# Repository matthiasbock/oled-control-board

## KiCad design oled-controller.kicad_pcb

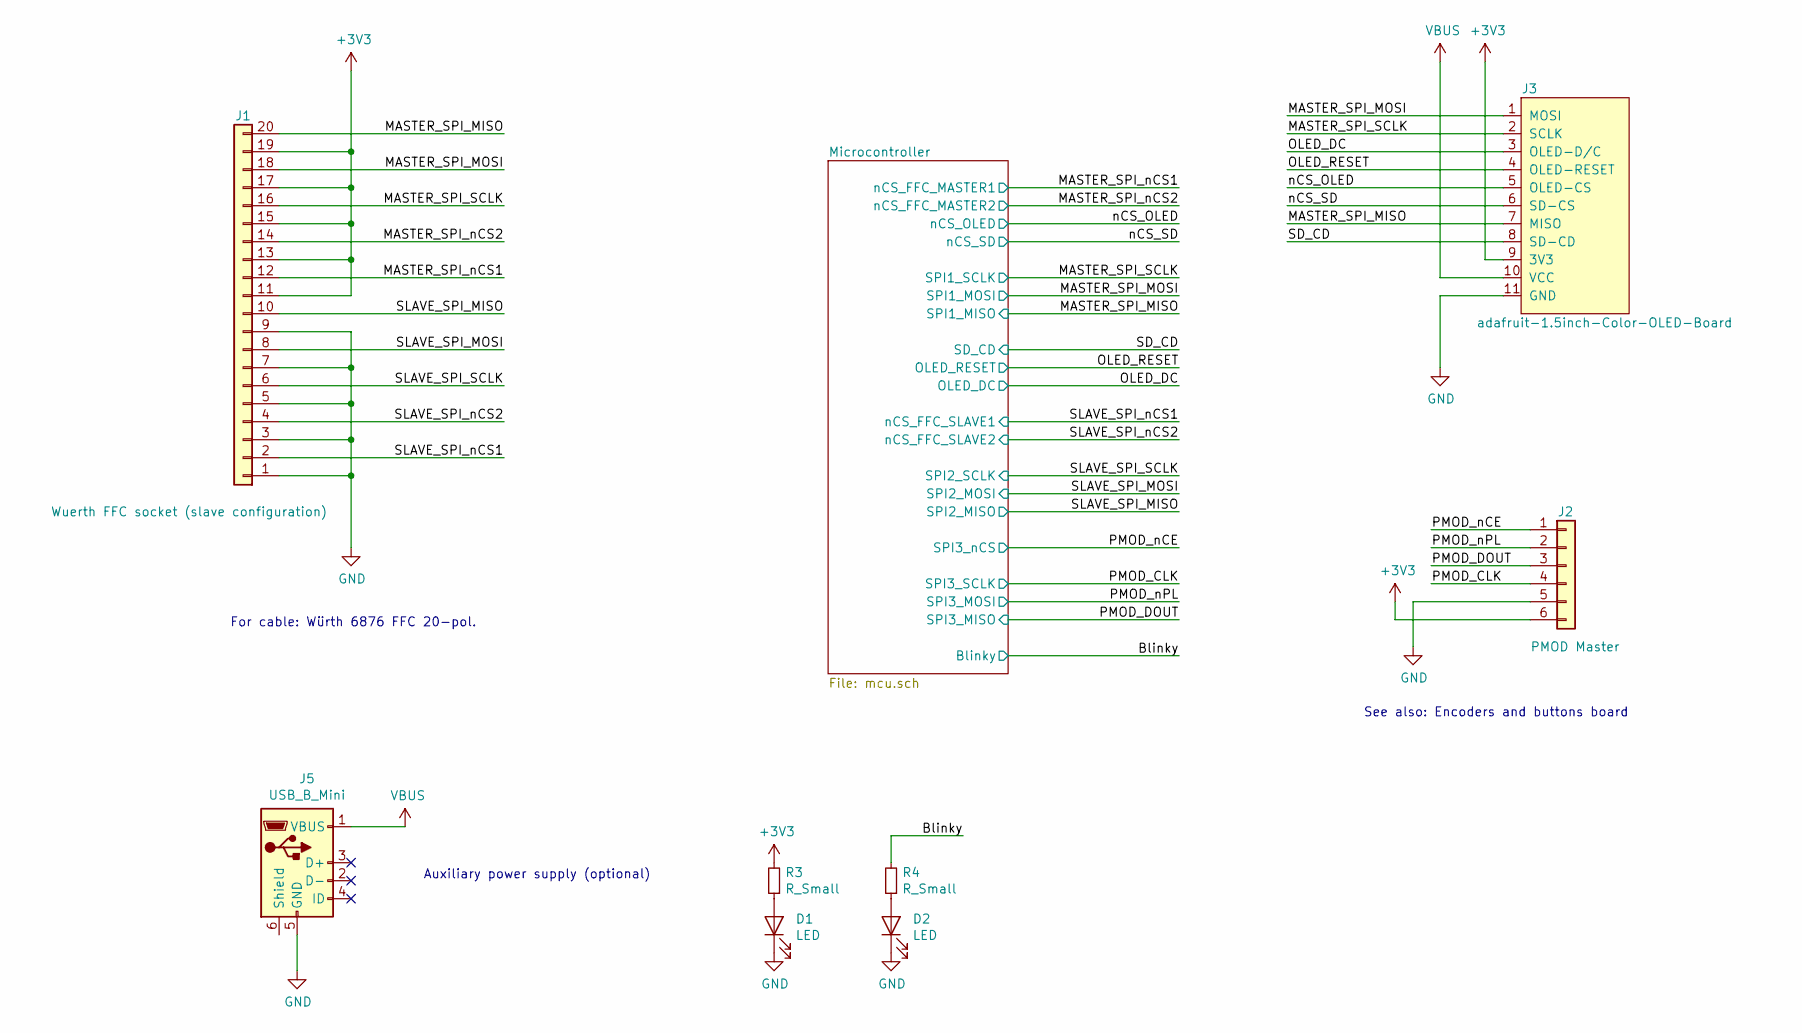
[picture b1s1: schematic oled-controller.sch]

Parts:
D1, D2: LED; D_0603_1608Metric_Pad1.05x0.95mm_HandSolder
J1: Wuerth FFC socket (slave configuration); Wuerth_687120149022_1x20-1MP_P0.5mm_Horizontal_Handsolder
J2: PMOD Master; PinHeader_1x06_P2.54mm_Vertical
J3: adafruit-1.5inch-Color-OLED-Board; Adafruit-1.5inch-Color-OLED-PCB
J5: USB_B_Mini; USB_Mini-B_Lumberg_2486_01_Horizontal
R3, R4: R_Small; R_0603_1608Metric_Pad1.05x0.95mm_HandSolder

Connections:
+3V3: J1.11, J1.13, J1.15, J1.17, J1.19, J2.6, J3.9 (3V3), R3.2; also elsewhere on the board
/Blinky: R4.2; also elsewhere on the board
/MASTER_SPI_MISO: J1.20, J3.7 (MISO); also elsewhere on the board
/MASTER_SPI_MOSI: J1.18, J3.1 (MOSI); also elsewhere on the board
/MASTER_SPI_SCLK: J1.16, J3.2 (SCLK); also elsewhere on the board
/MASTER_SPI_nCS1: J1.12; also elsewhere on the board
/MASTER_SPI_nCS2: J1.14; also elsewhere on the board
/OLED_DC: J3.3 (OLED-D/C); also elsewhere on the board
/OLED_RESET: J3.4 (OLED-RESET); also elsewhere on the board
/PMOD_CLK: J2.4; also elsewhere on the board
/PMOD_DOUT: J2.3; also elsewhere on the board
/PMOD_nCE: J2.1; also elsewhere on the board
/PMOD_nPL: J2.2; also elsewhere on the board
/SD_CD: J3.8 (SD-CD); also elsewhere on the board
/SLAVE_SPI_MISO: J1.10; also elsewhere on the board
/SLAVE_SPI_MOSI: J1.8; also elsewhere on the board
/SLAVE_SPI_SCLK: J1.6; also elsewhere on the board
/SLAVE_SPI_nCS1: J1.2; also elsewhere on the board
/SLAVE_SPI_nCS2: J1.4; also elsewhere on the board
/nCS_OLED: J3.5 (OLED-CS); also elsewhere on the board
/nCS_SD: J3.6 (SD-CS); also elsewhere on the board
GND: D1.1 (K), D2.1 (K), J1.1, J1.3, J1.5, J1.7, J1.9, J2.5, J3.11 (GND), J5.5 (GND); also elsewhere on the board
unnamed: D1.2 (A), R3.1
unnamed: D2.2 (A), R4.1
VBUS: J3.10 (VCC), J5.1 (VBUS)

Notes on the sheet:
For cable: Würth 6876 FFC 20-pol.
See also: Encoders and buttons board
Auxiliary power supply (optional)

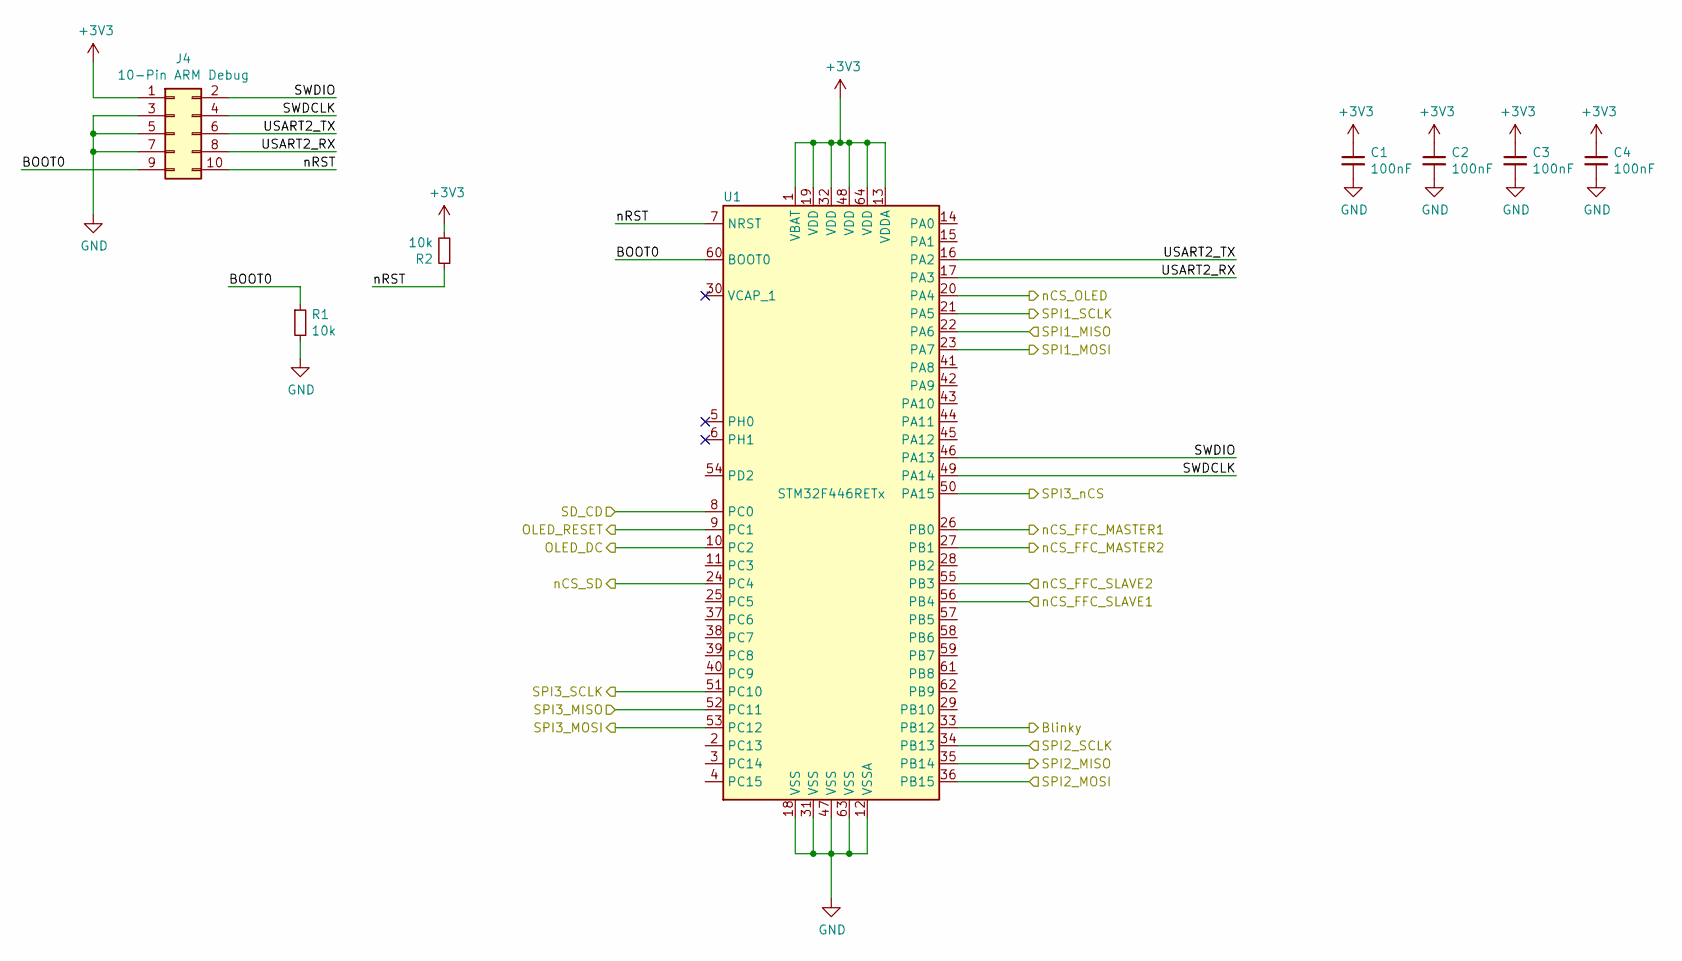
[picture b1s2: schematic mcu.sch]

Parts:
C1, C2, C3, C4: 100nF; C_0603_1608Metric_Pad1.05x0.95mm_HandSolder
J4: 10-Pin ARM Debug; PinHeader_2x05_P1.27mm_Vertical_SMD
R1, R2: 10k; R_0603_1608Metric_Pad1.05x0.95mm_HandSolder
U1: STM32F446RETx; LQFP-64_10x10mm_P0.5mm

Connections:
+3V3: C1.1, C2.1, C3.1, C4.1, J4.1, R2.2, U1.1 (VBAT), U1.13 (VDDA), U1.19 (VDD), U1.32 (VDD), U1.48 (VDD), U1.64 (VDD); also elsewhere on the board
/Blinky: U1.33 (PB12); also elsewhere on the board
/MASTER_SPI_MISO: U1.22 (PA6); also elsewhere on the board
/MASTER_SPI_MOSI: U1.23 (PA7); also elsewhere on the board
/MASTER_SPI_SCLK: U1.21 (PA5); also elsewhere on the board
/MASTER_SPI_nCS1: U1.26 (PB0); also elsewhere on the board
/MASTER_SPI_nCS2: U1.27 (PB1); also elsewhere on the board
/Microcontroller/BOOT0: J4.9, R1.1, U1.60 (BOOT0)
/Microcontroller/SWDCLK: J4.4, U1.49 (PA14)
/Microcontroller/SWDIO: J4.2, U1.46 (PA13)
/Microcontroller/USART2_RX: J4.8, U1.17 (PA3)
/Microcontroller/USART2_TX: J4.6, U1.16 (PA2)
/Microcontroller/nRST: J4.10, R2.1, U1.7 (NRST)
/OLED_DC: U1.10 (PC2); also elsewhere on the board
/OLED_RESET: U1.9 (PC1); also elsewhere on the board
/PMOD_CLK: U1.51 (PC10); also elsewhere on the board
/PMOD_DOUT: U1.52 (PC11); also elsewhere on the board
/PMOD_nCE: U1.50 (PA15); also elsewhere on the board
/PMOD_nPL: U1.53 (PC12); also elsewhere on the board
/SD_CD: U1.8 (PC0); also elsewhere on the board
/SLAVE_SPI_MISO: U1.35 (PB14); also elsewhere on the board
/SLAVE_SPI_MOSI: U1.36 (PB15); also elsewhere on the board
/SLAVE_SPI_SCLK: U1.34 (PB13); also elsewhere on the board
/SLAVE_SPI_nCS1: U1.56 (PB4); also elsewhere on the board
/SLAVE_SPI_nCS2: U1.55 (PB3); also elsewhere on the board
/nCS_OLED: U1.20 (PA4); also elsewhere on the board
/nCS_SD: U1.24 (PC4); also elsewhere on the board
GND: C1.2, C2.2, C3.2, C4.2, J4.3, J4.5, J4.7, R1.2, U1.12 (VSSA), U1.18 (VSS), U1.31 (VSS), U1.47 (VSS), U1.63 (VSS); also elsewhere on the board

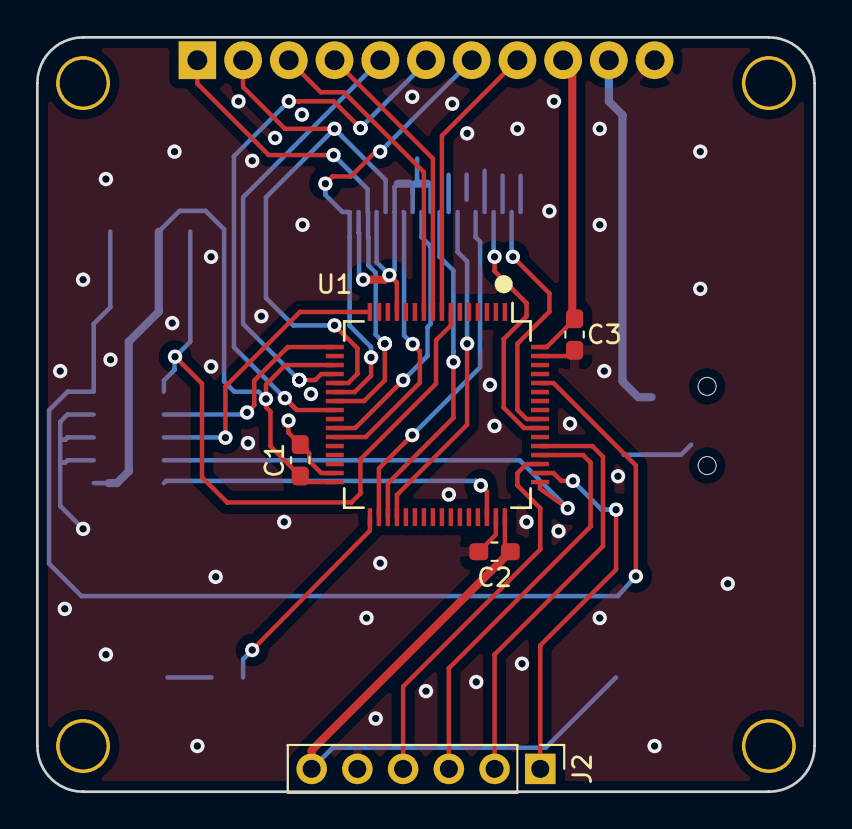
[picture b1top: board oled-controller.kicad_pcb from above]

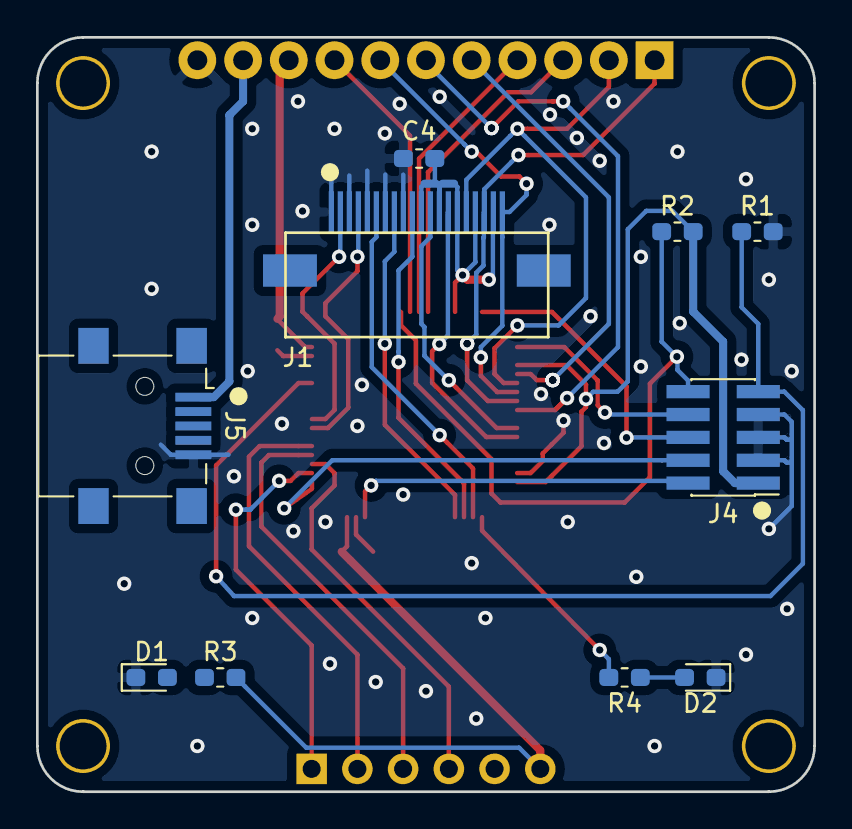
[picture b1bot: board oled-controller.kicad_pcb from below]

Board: 2 copper layers, 43.2 x 41.9 mm, 16 parts (10 on the bottom side), 31 nets.

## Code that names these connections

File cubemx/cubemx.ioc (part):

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Mcu.Name=STM32F446R(C-E)Tx
Mcu.Package=LQFP64
Mcu.UserName=STM32F446RETx
PA13.Mode=Serial_Wire
PA13.Signal=SYS_JTMS-SWDIO
PA14.Mode=Serial_Wire
PA14.Signal=SYS_JTCK-SWCLK
PA15.Mode=NSS_Signal_Hard_Output
PA15.Signal=SPI3_NSS
PA2.Mode=Asynchronous
PA2.Signal=USART2_TX
PA3.Mode=Asynchronous
PA3.Signal=USART2_RX
PA4.Signal=SPI1_NSS
PA5.Mode=Full_Duplex_Master
PA5.Signal=SPI1_SCK
PA6.Mode=Full_Duplex_Master
PA6.Signal=SPI1_MISO
PA7.Mode=Full_Duplex_Master
PA7.Signal=SPI1_MOSI
PB0.Signal=GPIO_Output
PB1.Signal=GPIO_Output
PB13.Mode=Full_Duplex_Master
PB13.Signal=SPI2_SCK
PB14.Mode=Full_Duplex_Master
PB14.Signal=SPI2_MISO
PB15.Mode=Full_Duplex_Master
PB15.Signal=SPI2_MOSI
PB3.Signal=GPIO_Input
PB4.Signal=SPI2_NSS
PC0.Signal=GPIO_Input
PC1.Signal=GPIO_Output
PC10.Mode=Full_Duplex_Master
PC10.Signal=SPI3_SCK
PC11.Mode=Full_Duplex_Master
PC11.Signal=SPI3_MISO
PC12.Mode=Full_Duplex_Master
PC12.Signal=SPI3_MOSI
PC2.Signal=GPIO_Output
PC4.Signal=GPIO_Output
PC5.Signal=GPIO_Output
RCC.SYSCLKFreq_VALUE=180000000
RCC.SYSCLKSource=RCC_SYSCLKSOURCE_PLLCLK

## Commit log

2019-03-01 Added my KiCad libraries as submodule
2019-03-01 Began empty KiCad 5 project
2019-03-29 Added FT2232D and OLED connector
2019-03-29 Added block diagram
2019-03-29 Moved USB and ESD protection to debugger schematic
2019-03-31 Added CubeMX project
2019-03-31 Added hierarchical ports for SPI1-3 and others
2019-03-31 Added pinout screenshot from CubeMX
2019-03-31 Added PMOD connector and bypass capacitors
2019-04-03 Updated library
2019-04-03 Added Adafruit OLED display board design files as submodule
2019-04-03 Completed schematic adjustments and layouting
2019-04-04 Updated connection diagram
2019-04-04 Added two LEDs
2019-04-04 Moved pinout.png to cubemx/
2019-04-05 PCB: Final adjustments
2019-04-05 Exported fabrication files for revision 1
2019-04-19 Added schematic PDF and plotted silkscreen layers
2019-04-19 Renamed rev1/ -> v1.0/
2019-07-11 Added CERN Open Hardware Licence v1.2
